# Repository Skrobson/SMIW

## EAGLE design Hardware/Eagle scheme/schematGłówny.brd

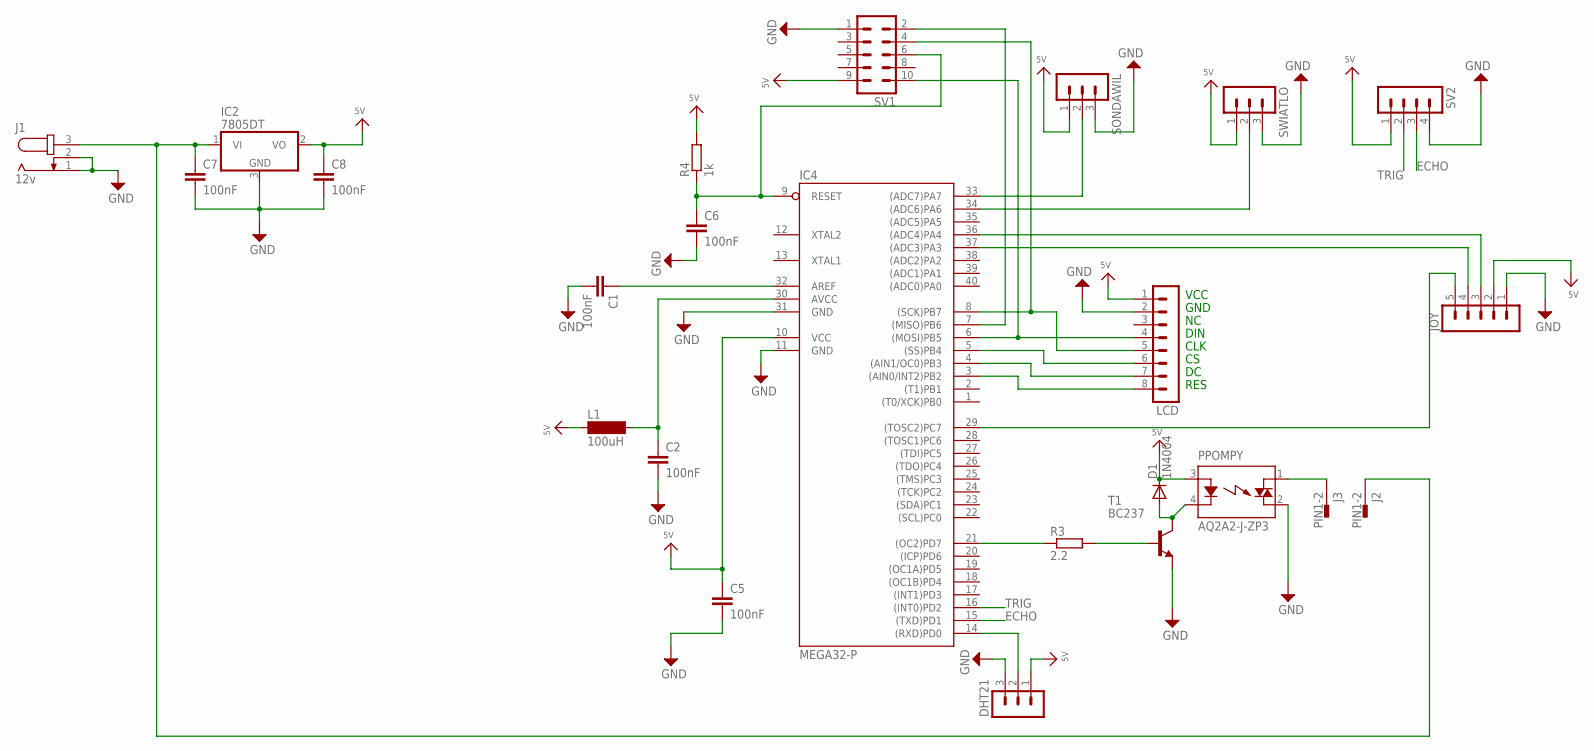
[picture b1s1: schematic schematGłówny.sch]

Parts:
C1, C2, C5, C6, C7, C8: 100nF; C2.5-6
D1: 1N4004; DO41-10
DHT21: MA03-1
IC2: 7805DT; TO252
IC4: MEGA32-P; DIL40
J1: 12v; SPC4078
J2, J3: PIN1-2; 62221
JOY: MA05-1
L1: 100uH; BS75
LCD: MA08-1
PPOMPY: AQ2A2-J-ZP3; AQ1-FLAT
R3: 2.2; 0207/15
R4: 1k; 0207/15
SONDAWIL: MA03-1
SV1: MA05-2
SV2: MA04-1
SWIATLO: MA03-1
T1: BC237; TO92

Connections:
ECHO: IC4.15 ((TXD)PD1), SV2.3
GND: C1.2, C2.2, C5.2, C6.2, C7.2, C8.2, DHT21.3, IC2.3 (GND), IC4.11 (GND), IC4.31 (GND), J1.1, J1.2, JOY.1, LCD.2, PPOMPY.2 (DS2), SONDAWIL.3, SV1.1, SV2.4, SWIATLO.3, T1.1 (E)
unnamed: C6.1, IC4.9 (RESET), R4.1, SV1.6
unnamed: IC4.6 ((MOSI)PB5), LCD.4, SV1.10
unnamed: C1.1, IC4.32 (AREF)
unnamed: C2.1, IC4.30 (AVCC), L1.2
unnamed: IC4.8 ((SCK)PB7), LCD.5, SV1.4
unnamed: IC4.5 ((SS)PB4), LCD.6
unnamed: IC4.4 ((AIN1/OC0)PB3), LCD.7
unnamed: IC4.3 ((AIN0/INT2)PB2), LCD.8
unnamed: DHT21.2, IC4.14 ((RXD)PD0)
unnamed: IC4.33 ((ADC7)PA7), SONDAWIL.2
unnamed: IC4.34 ((ADC6)PA6), SWIATLO.2
unnamed: IC4.21 ((OC2)PD7), R3.1
unnamed: R3.2, T1.2 (B)
unnamed: IC4.29 ((TOSC2)PC7), JOY.5
unnamed: IC4.37 ((ADC3)PA3), JOY.4
unnamed: IC4.36 ((ADC4)PA4), JOY.3
unnamed: D1.A, PPOMPY.4 (K), T1.3 (C)
unnamed: IC4.7 ((MISO)PB6), SV1.2
unnamed: J3.1, PPOMPY.1 (DS1)
unnamed: C7.1, IC2.1 (VI), J1.3, J2.1
TRIG: IC4.16 ((INT0)PD2), SV2.2
VCC: C5.1, C8.1, D1.C, DHT21.1, IC2.2 (VO), IC4.10 (VCC), JOY.2, L1.1, LCD.1, PPOMPY.3 (A), R4.2, SONDAWIL.1, SV1.9, SV2.1, SWIATLO.1

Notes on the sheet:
DIN
CLK
RES
VCC
GND

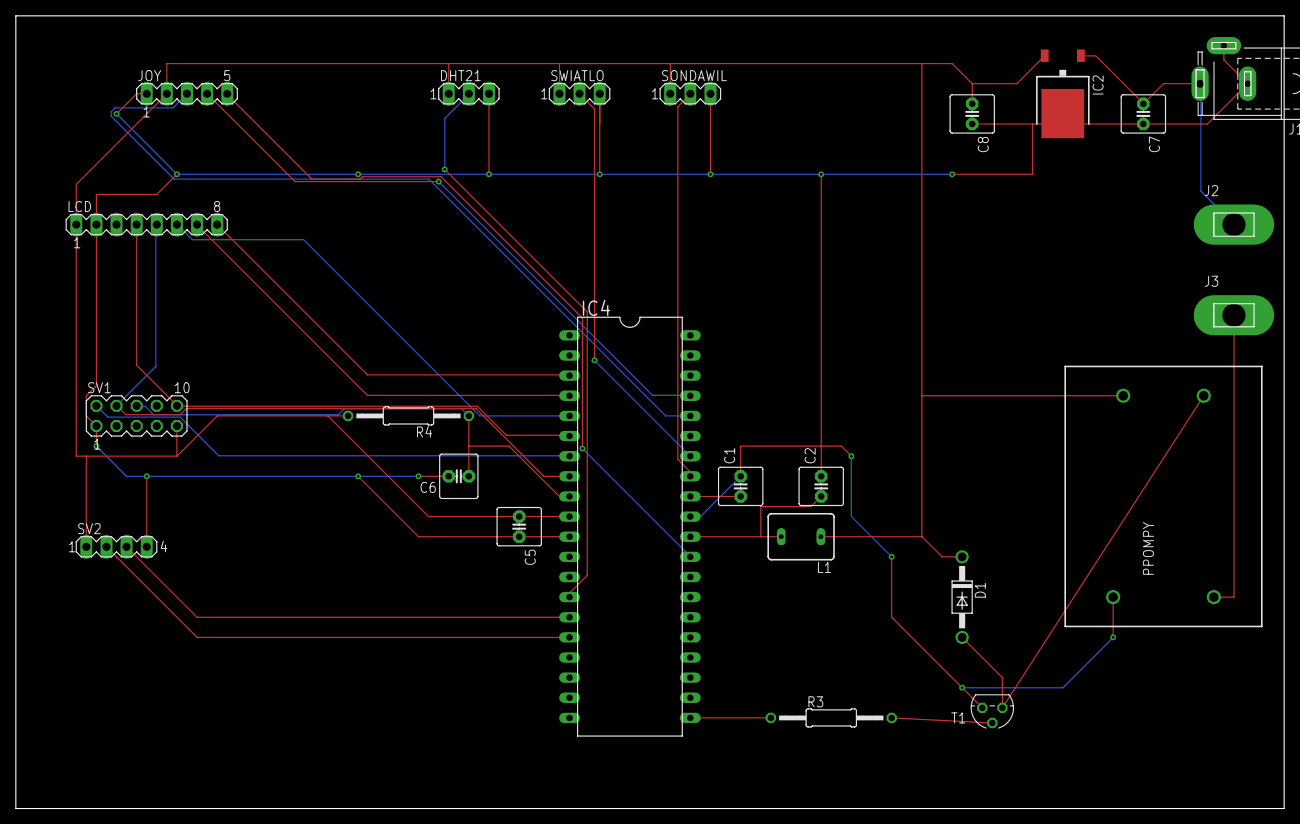
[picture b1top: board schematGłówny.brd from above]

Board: 2 copper layers, 160.0 x 100.0 mm, 24 parts (0 on the bottom side), 24 nets.

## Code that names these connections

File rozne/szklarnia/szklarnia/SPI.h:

/*
 * SPI.h
 *
 * Created: 2018-04-24 21:55:27
 *  Author: T530
 */ 

#ifndef SPI
#define SPI
#include <avr/io.h>

#ifndef csPORT
# warning "Define csPORT (default PORTB)"
#define csPort PORTB
#endif

#ifndef cs1 
# warning "Define cs1 if needed"
#define cs1 0
#endif

#ifndef cs2
# warning "Define cs2 if needed"
#define cs2 0
#endif

#ifndef cs3
# warning "Define cs3 if needed"
#define cs3 0
#endif


#define SCK 	PB7		//sygna³ zegarowy SCK
#define MISO 	PB6		//sygna³ MISO - Master Input Slave Output
#define MOSI	PB5		//sygna³ MOSI - Master Output Slave Input
#define SS		PB4		//sygna³ wyboru mikrokontrolera dla pracy w trybie Slave
#define OLED_DC	    PB3
#define OLED_RES    PB2

char dataIn;

void spiInitMaster(void){

	DDRB |= (1<<SCK)|(1<<MOSI)|(1<<SS)|(1<<OLED_DC)|(1<<OLED_DC);    // SCK, MOSI and SS as outputs
	DDRB &= ~(1<<4);                 // MISO as input
	
	
	SPCR |= (1<<MSTR);               // Set as Master
	SPCR |= (1<<SPR0)|(1<<SPR1);     // divided clock by 128
	SPCR |= (1<<SPE);                // Enable SPI
}

void spiInitSlave(void){

	DDRB &= ~((1<<2)|(1<<3)|(1<<5));   // SCK, MOSI and SS as inputs
	DDRB |= (1<<4);                    // MISO as output

	SPCR &= ~(1<<MSTR);                // Set as slave
	SPCR |= (1<<SPR0)|(1<<SPR1);       // divide clock by 128
	SPCR |= (1<<SPE);
	
	SPSR = (1<<SPI2X);  
}

int spiReceive(void){//Call in while(1)
	while(!(SPSR & (1<<SPIF)));    // wait until all data is received
	dataIn = SPDR;
	return dataIn;
}

void spiTransmit(char dataOut, int slavePin){//Call in while(1)
	csPort &= ~ 1<<slavePin;
	SPDR = dataOut;                 // send the data
	while(!(SPSR & (1<<SPIF)));
}
#endif

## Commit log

2018-07-17 init
2018-08-08 working distance sensor
2018-08-12 usunieto niepotrzebne pliki
2018-08-12 datasheet
2018-09-02 działający projekt
2018-09-02 wytyczne raportu
2018-09-03 nazwa folderu byla niedozwolaona na windows
2018-09-07 dokumentacja
2018-09-08 skonczona dokumentacja
2018-09-08 reorgamizacja folderów
2018-09-08 reorganizacja projektu
2018-09-15 Schemat PCB

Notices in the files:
parts and their libraries:
MAX9812: License : GNU General Public License version 2 (see bottom)
